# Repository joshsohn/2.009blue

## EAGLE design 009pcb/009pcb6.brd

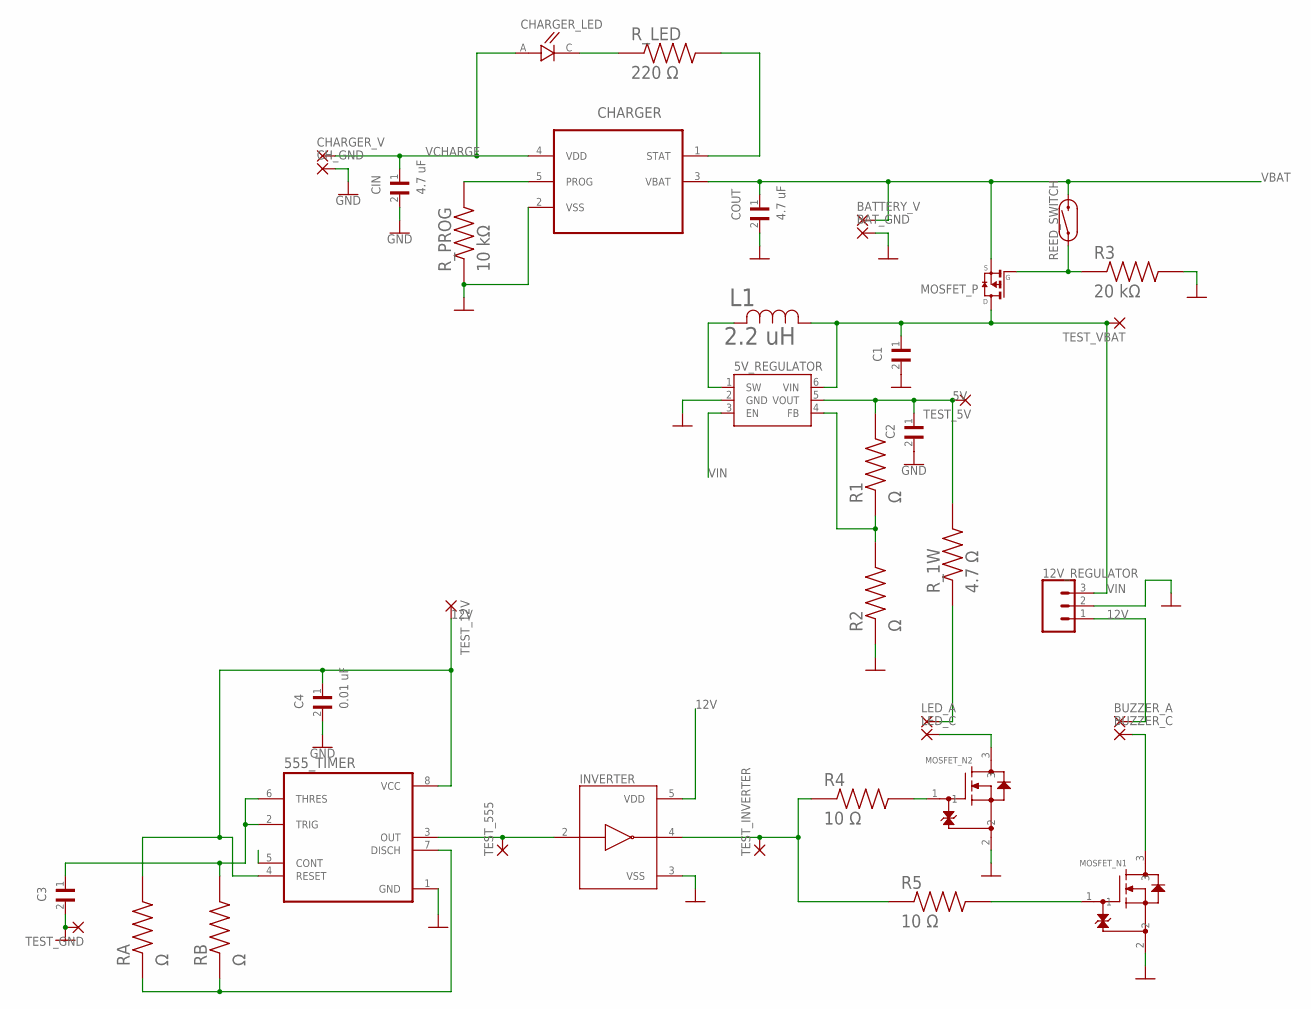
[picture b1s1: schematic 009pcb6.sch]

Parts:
5V_REGULATOR: TLV61070ASOT-23; SOT23-6
12V_REGULATOR: CONN_03; 1X03
555_TIMER: NE555DR; SOIC127P599X175-8N
BATTERY_V: WIREPADSMD1,27-254; SMD1,27-2,54
BAT_GND: WIREPADSMD1,27-254; SMD1,27-2,54
BUZZER_A: WIREPADSMD1,27-254; SMD1,27-2,54
BUZZER_C: WIREPADSMD1,27-254; SMD1,27-2,54
C1, C2, C3: GRT21BR61H475ME13L; CAPC2012X135N
C4: 0.01 uF; CAPC2012X135N
CHARGER: MCP73831T-5ACI/OT; SOT95P280X145-5N
CHARGER_LED: 5988170107F; LEDC2012X70N
CHARGER_V: WIREPADSMD1,27-254; SMD1,27-2,54
CH_GND: WIREPADSMD1,27-254; SMD1,27-2,54
CIN: 4.7 uF; CAPC2012X135N
COUT: 4.7 uF; CAPC2012X135N
INVERTER: BU4SU69G2-TR; SOT95P280X125-5N
L1: 2.2 uH; IND_8357022_WRE
LED_A: WIREPADSMD1,27-254; SMD1,27-2,54
LED_C: WIREPADSMD1,27-254; SMD1,27-2,54
MOSFET_N1, MOSFET_N2: SSM3K335R; SOT-23F_TOS
MOSFET_P: DMP2004K; SOT23
R1, R2: Ω; RESC2012X60N
R3: 20 kΩ; RESC2012X60N
R4, R5: 10 Ω; RESC2012X60N
RA: Ω; RESC2012X60N
RB: Ω; RESC2012X60N
REED_SWITCH: REED_SWITCH-PTH-GLASS; REED_SWITCH_GLASS
R_1W: 4.7 Ω; RESC6331X65N
R_LED: 220 Ω; RESC2012X60N
R_PROG: 10 kΩ; RESC2012X60N
TEST_5V, TEST_12V, TEST_555: WIREPADSMD1,27-254; SMD1,27-2,54
TEST_GND: WIREPADSMD1,27-254; SMD1,27-2,54
TEST_INVERTER: WIREPADSMD1,27-254; SMD1,27-2,54
TEST_VBAT: WIREPADSMD1,27-254; SMD1,27-2,54

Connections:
5V: 5V_REGULATOR.5 (VOUT), C2.1, R1.2, R_1W.2, TEST_5V.1
12V: 12V_REGULATOR.1, 555_TIMER.4 (RESET), 555_TIMER.8 (VCC), BUZZER_A.1, C4.1, INVERTER.5 (VDD), RA.2, TEST_12V.1
GND: 5V_REGULATOR.2 (GND), 12V_REGULATOR.2, 555_TIMER.1 (GND), BAT_GND.1, C1.2, C2.2, C3.2, C4.2, CHARGER.2 (VSS), CH_GND.1, CIN.2, COUT.2, INVERTER.3 (VSS), MOSFET_N1.2, MOSFET_N2.2, R2.1, R3.2, R_PROG.1, TEST_GND.1
unnamed: CHARGER.5 (PROG), R_PROG.2
unnamed: CHARGER_LED.C, R_LED.1
unnamed: MOSFET_P.1 (G), R3.1, REED_SWITCH.P$1 (1)
unnamed: CHARGER.1 (STAT), R_LED.2
unnamed: 555_TIMER.2 (TRIG), 555_TIMER.6 (THRES), C3.1, RB.2
unnamed: LED_A.1, R_1W.1
unnamed: 555_TIMER.7 (DISCH), RA.1, RB.1
unnamed: 5V_REGULATOR.1 (SW), L1.2
unnamed: 555_TIMER.3 (OUT), INVERTER.2 (A), TEST_555.1
unnamed: 5V_REGULATOR.4 (FB), R1.1, R2.2
unnamed: INVERTER.4 (Y), R4.1, R5.1, TEST_INVERTER.1
unnamed: MOSFET_N2.1, R4.2
unnamed: LED_C.1, MOSFET_N2.3
unnamed: MOSFET_N1.1, R5.2
unnamed: BUZZER_C.1, MOSFET_N1.3
VBAT: BATTERY_V.1, CHARGER.3 (VBAT), COUT.1, MOSFET_P.2 (S), REED_SWITCH.P$2 (2)
VCHARGE: CHARGER.4 (VDD), CHARGER_LED.A, CHARGER_V.1, CIN.1
VIN: 5V_REGULATOR.3 (EN), 5V_REGULATOR.6 (VIN), 12V_REGULATOR.3, C1.1, L1.1, MOSFET_P.3 (D), TEST_VBAT.1

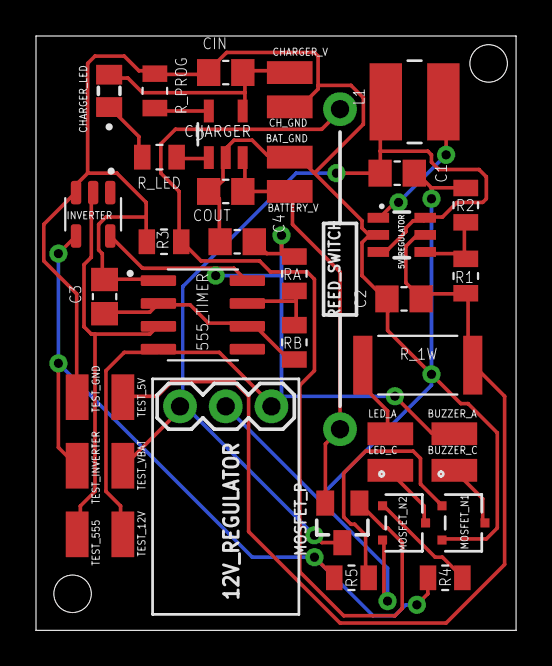
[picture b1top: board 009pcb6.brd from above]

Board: 2 copper layers, 26.7 x 33.0 mm, 41 parts (0 on the bottom side), 21 nets.

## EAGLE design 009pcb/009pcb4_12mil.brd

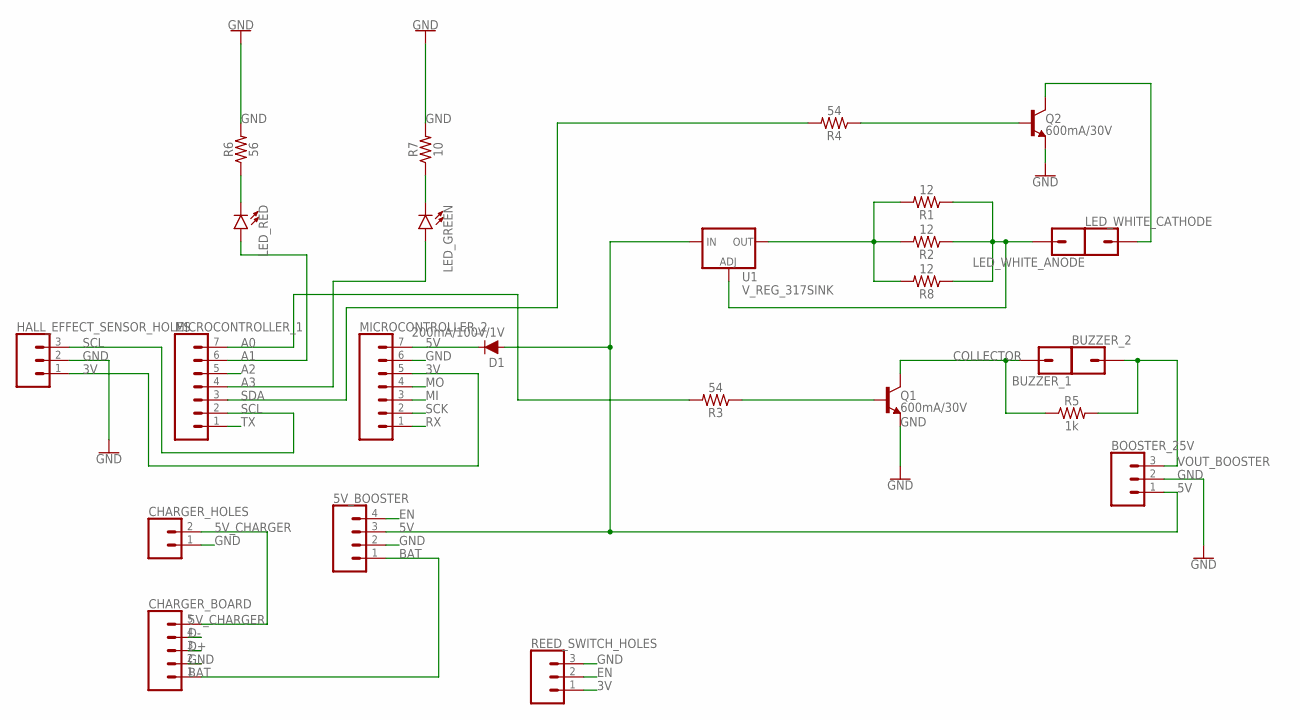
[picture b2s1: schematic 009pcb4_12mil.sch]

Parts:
5V_BOOSTER: CONN_04; 1X04
BOOSTER_25V: CONN_03; 1X03
BUZZER_1, BUZZER_2: CONN_01; 1X01
CHARGER_BOARD: CONN_05; 1X05
CHARGER_HOLES: CONN_02; 1X02
D1: 200mA/100V/1V; DIODE-1N4148
HALL_EFFECT_SENSOR_HOLES: CONN_03; 1X03
LED_GREEN: LED5MM; LED_5MM
LED_RED: LED5MM; LED_5MM
LED_WHITE_ANODE: CONN_01; 1X01
LED_WHITE_CATHODE: CONN_01; 1X01
MICROCONTROLLER_1, MICROCONTROLLER_2: CONN_07; 1X07
Q1, Q2: 600mA/30V; TO-92
R1, R2, R8: 12; AXIAL-0.3
R3, R4: 54; AXIAL-0.3
R5: 1k; AXIAL-0.3
R6: 56; AXIAL-0.3
R7: 10; AXIAL-0.3
REED_SWITCH_HOLES: CONN_03; 1X03
U1: V_REG_317SINK; TO220-ADJ

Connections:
3V: HALL_EFFECT_SENSOR_HOLES.1, MICROCONTROLLER_2.5, REED_SWITCH_HOLES.1
5V: 5V_BOOSTER.3, BOOSTER_25V.1, D1.A, U1.IN
5V_CHARGER: CHARGER_BOARD.5, CHARGER_HOLES.2
A0: MICROCONTROLLER_1.7, R3.P$2 (2)
A1: LED_RED.A, MICROCONTROLLER_1.6
A2: MICROCONTROLLER_1.5
A3: LED_GREEN.A, MICROCONTROLLER_1.4
ADJUST: LED_WHITE_ANODE.1, R1.P$1 (1), R2.P$1 (1), R8.P$1 (1), U1.ADJ
BASE: Q1.2 (B), Q2.2 (B), R3.P$1 (1), R4.P$1 (1)
BAT: 5V_BOOSTER.1, CHARGER_BOARD.1
COLLECTOR: BUZZER_1.1, LED_WHITE_CATHODE.1, Q1.3 (C), Q2.3 (C), R5.P$1 (1)
D+: CHARGER_BOARD.3
D-: CHARGER_BOARD.4
EN: 5V_BOOSTER.4, REED_SWITCH_HOLES.2
GND: 5V_BOOSTER.2, BOOSTER_25V.2, CHARGER_BOARD.2, CHARGER_HOLES.1, HALL_EFFECT_SENSOR_HOLES.2, MICROCONTROLLER_2.6, Q1.1 (E), Q2.1 (E), R6.P$2 (2), R7.P$2 (2), REED_SWITCH_HOLES.3
MI: MICROCONTROLLER_2.3
MO: MICROCONTROLLER_2.4
unnamed: LED_RED.K (C), R6.P$1 (1)
unnamed: LED_GREEN.K (C), R7.P$1 (1)
unnamed: D1.C, MICROCONTROLLER_2.7
RX: MICROCONTROLLER_2.1
SCK: MICROCONTROLLER_2.2
SCL: HALL_EFFECT_SENSOR_HOLES.3, MICROCONTROLLER_1.2
SDA: MICROCONTROLLER_1.3, R4.P$2 (2)
TX: MICROCONTROLLER_1.1
VOUT_BOOSTER: BOOSTER_25V.3, BUZZER_2.1, R5.P$2 (2)
VOUT_LM317: R1.P$2 (2), R2.P$2 (2), R8.P$2 (2), U1.OUT

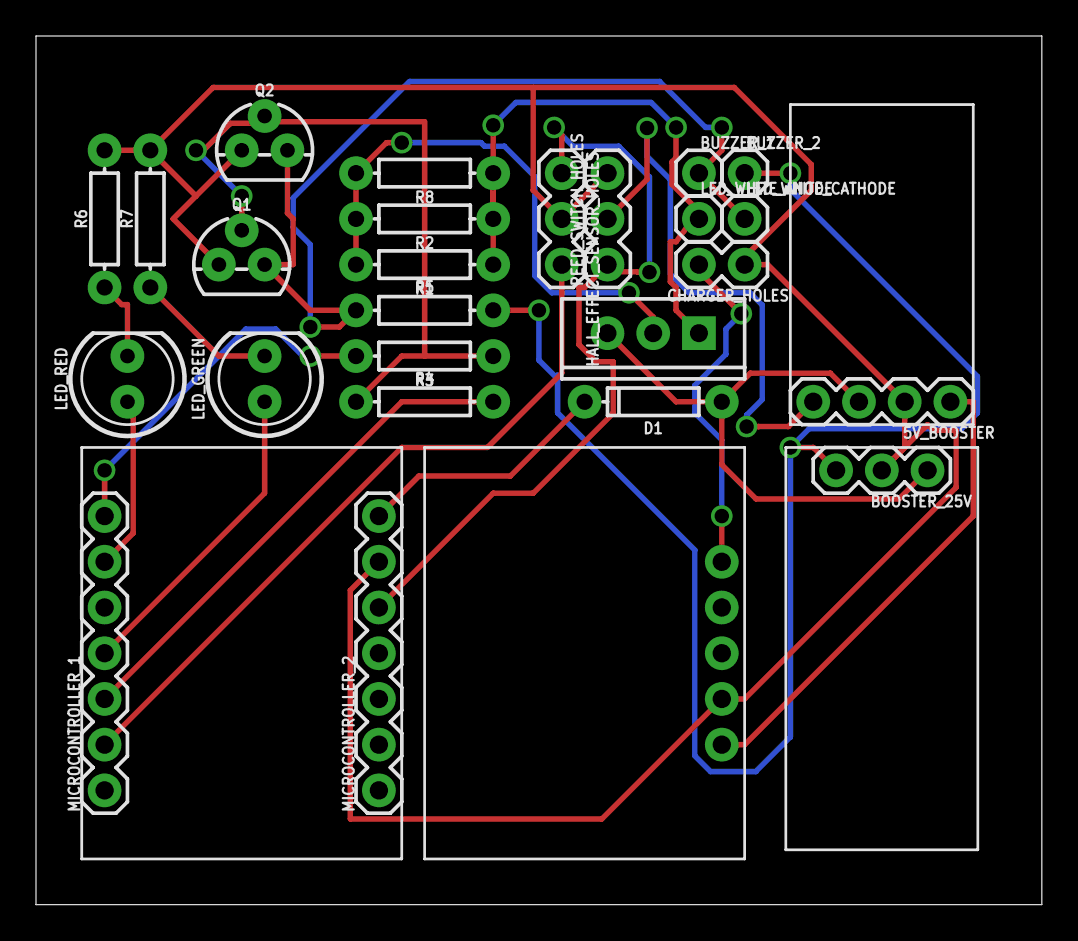
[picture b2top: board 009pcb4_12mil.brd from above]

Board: 2 copper layers, 55.9 x 48.3 mm, 26 parts (1 on the bottom side), 19 nets.

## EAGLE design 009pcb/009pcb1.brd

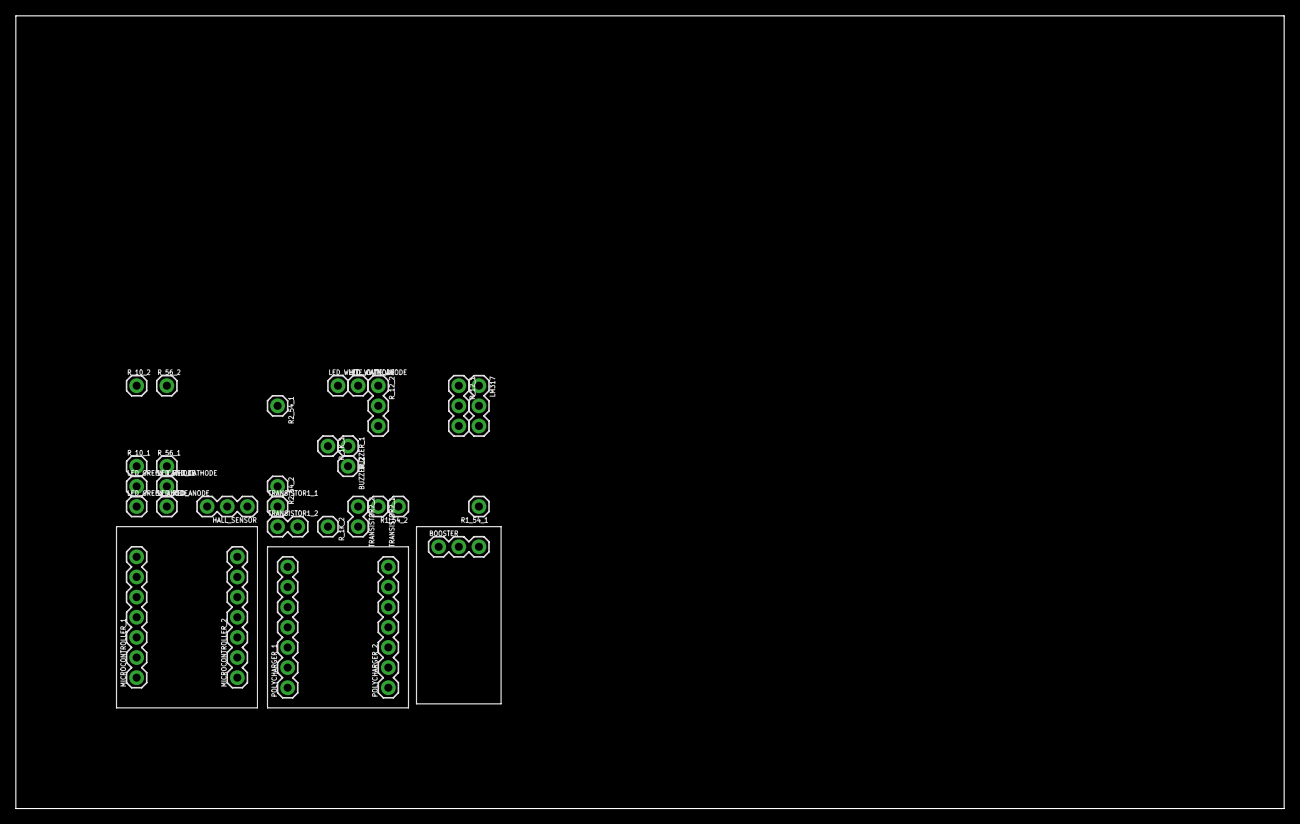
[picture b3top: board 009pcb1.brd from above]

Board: 2 copper layers, 160.0 x 100.0 mm, 31 parts (0 on the bottom side), 16 nets, no tracks yet.

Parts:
BOOSTER: 1X03
BUZZER_1, BUZZER_2: 1X01
HALL_SENSOR: 1X03
LED_GREEN_ANODE: 1X01
LED_GREEN_CATHODE: 1X01
LED_RED_ANODE: 1X01
LED_RED_CATHODE: 1X01
LED_WHITE_ANODE: 1X01
LED_WHITE_CATHODE: 1X01
LM317: 1X03
MICROCONTROLLER_1, MICROCONTROLLER_2: 1X07
POLYCHARGER_1, POLYCHARGER_2: 1X07
R1_54_1, R1_54_2, R2_54_1, R2_54_2: 1X01
R_1K_1, R_1K_2, R_10_1, R_10_2, R_56_1, R_56_2: 1X01
R_12_1, R_12_2: 1X03
TRANSISTOR1_1, TRANSISTOR2_1: 1X01
TRANSISTOR1_2, TRANSISTOR2_2: 1X02

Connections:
5V: MICROCONTROLLER_2.7, POLYCHARGER_1.7
A0: MICROCONTROLLER_1.7, R2_54_1.1
A1: LED_RED_ANODE.1, MICROCONTROLLER_1.6
A2: MICROCONTROLLER_1.5, POLYCHARGER_2.5
A3: LED_GREEN_ANODE.1, MICROCONTROLLER_1.4
ADJUST: LED_WHITE_ANODE.1, LM317.1, R_12_2.1, R_12_2.2, R_12_2.3
BASE: R1_54_2.1, R2_54_2.1, TRANSISTOR1_1.1, TRANSISTOR2_1.1
CATHODE_G: LED_GREEN_CATHODE.1, R_10_1.1
CATHODE_R: LED_RED_CATHODE.1, R_56_1.1
COLLECTOR: BUZZER_1.1, LED_WHITE_CATHODE.1, R_1K_1.1, TRANSISTOR1_2.2, TRANSISTOR2_2.2
GND: BOOSTER.2, HALL_SENSOR.2, MICROCONTROLLER_2.6, POLYCHARGER_1.6, R_10_2.1, R_56_2.1, TRANSISTOR1_2.1, TRANSISTOR2_2.1
LIPO: BOOSTER.1, HALL_SENSOR.1, LM317.3, POLYCHARGER_1.2
SCL: HALL_SENSOR.3, MICROCONTROLLER_1.2
SDA: MICROCONTROLLER_1.3, R1_54_1.1
VOUT_BOOSTER: BOOSTER.3, BUZZER_2.1, R_1K_2.1
VOUT_LM317: LM317.2, R_12_1.1, R_12_1.2, R_12_1.3

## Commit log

2022-11-08 first push!
2022-11-08 second commit lmao
2022-11-08 fixed accelerometer
2022-11-13 added OLED + IMU
2022-11-14 added IMU
2022-11-19 pcb board
2022-11-20 pcb4 is the most updated version
2022-11-20 Added blink and buzzer code
2022-11-28 Added Sparkfun Libraries
2022-11-29 Reorganized Folders and Added a sparkfun eagle script
2022-11-29 Added the sparkfun eagle keybinds
2022-11-30 009pcb6 and eagle libraries
2022-11-30 cleaned up old pcb files
2022-12-01 009pcb6.brd
2022-12-02 sent for manufacturing
2022-12-06 final pcb brd and sch

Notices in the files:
parts and their libraries:
SparkFun-Connectors: Licensing: Creative Commons ShareAlike 4.0 International - https://creativecommons.org/licenses/by-sa/4.0
COPYRIGHT: Copyright (C) 2022 Ultra Librarian. All rights reserved.
